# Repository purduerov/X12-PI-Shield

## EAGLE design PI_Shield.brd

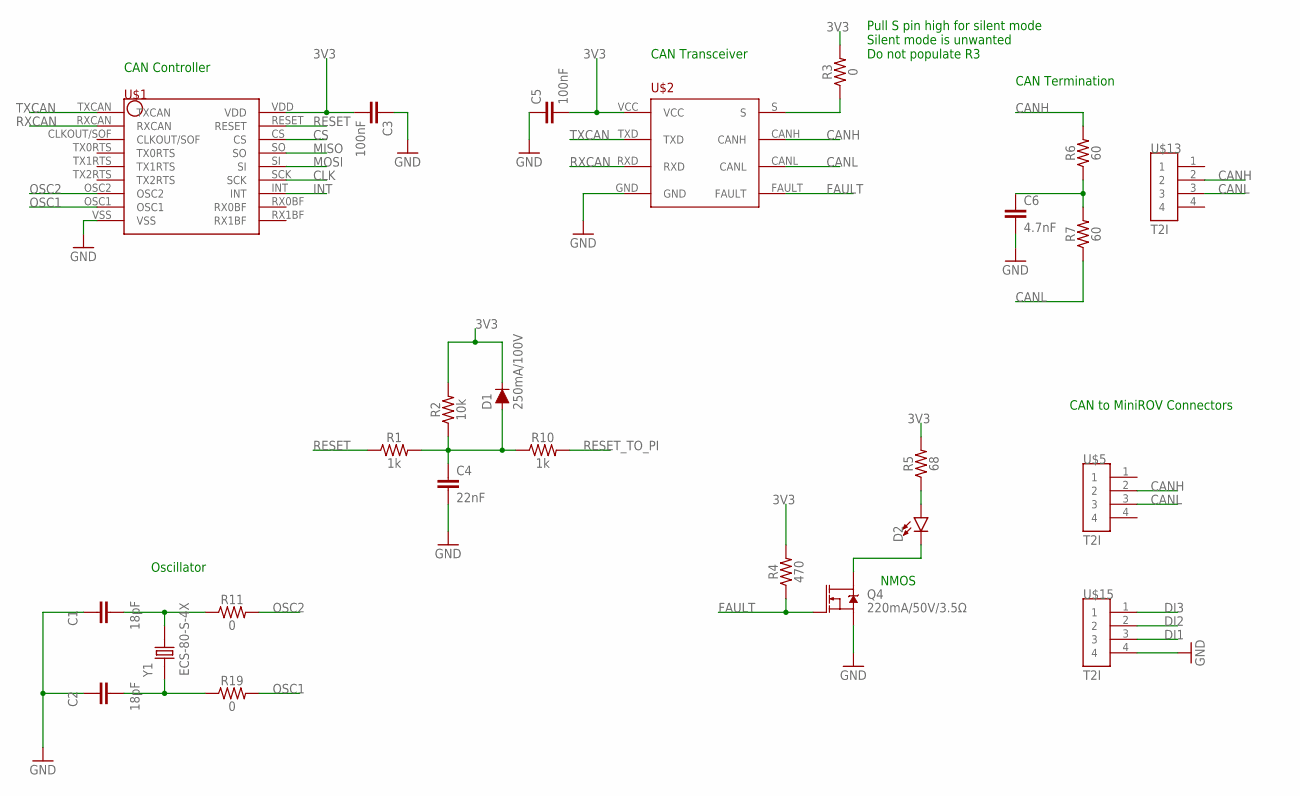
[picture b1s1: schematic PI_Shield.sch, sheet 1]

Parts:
C1, C2: 18pF; CAP_0603
C3, C5: 100nF; 0603
C4: 22nF; 0603
C6: 4.7nF; 0603
D1: 250mA/100V; SOD-323
D2: LED0603; LED-0603
Q4: 220mA/50V/3.5Ω; SOT23-3
R1, R10: 1k; 0603
R2: 10k; 0603
R3, R11, R19: 0; 0603
R4: 470; 0603
R5: 68; 0603
R6, R7: 60; 0603
U$1: MCP2515
U$2: TCAN337D
U$5, U$13, U$15: T2I
Y1: ECS-80-S-4X; XTAL_ECS-80-S-4X

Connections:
3V3: C3.2, C5.2, D1.C, R2.2, R3.2, R4.2, R5.2, U$1.VDD, U$2.VCC; also elsewhere on the board
CANH: R6.2, U$2.CANH, U$5.2, U$13.2; also elsewhere on the board
CANL: R7.1, U$2.CANL, U$5.3, U$13.3; also elsewhere on the board
CLK: U$1.SCK; also elsewhere on the board
CS: U$1.CS; also elsewhere on the board
DI1: U$15.3; also elsewhere on the board
DI2: U$15.2; also elsewhere on the board
DI3: U$15.1; also elsewhere on the board
FAULT: Q4.1 (G), R4.1, U$2.FAULT
GND: C1.1, C2.1, C3.1, C4.2, C5.1, C6.2, Q4.2 (S), U$1.VSS, U$2.GND, U$15.4; also elsewhere on the board
INT: U$1.INT; also elsewhere on the board
MISO: U$1.SO; also elsewhere on the board
MOSI: U$1.SI; also elsewhere on the board
unnamed: R3.1, U$2.S
unnamed: C1.2, R11.1, Y1.2
unnamed: C2.2, R19.1, Y1.1
unnamed: C6.1, R6.1, R7.2
unnamed: D2.C, Q4.3 (D)
unnamed: D2.A, R5.1
unnamed: C4.1, D1.A, R1.2, R2.1, R10.1
OSC1: R19.2, U$1.OSC1
OSC2: R11.2, U$1.OSC2
RESET: R1.1, U$1.RESET
RESET_TO_PI: R10.2; also elsewhere on the board
RXCAN: U$1.RXCAN, U$2.RXD
TXCAN: U$1.TXCAN, U$2.TXD

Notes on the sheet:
Oscillator
CAN Controller
CAN Transceiver
CAN Termination
CAN to MiniROV Connectors
NMOS
Pull S pin high for silent mode Silent mode is unwanted Do not populate R3

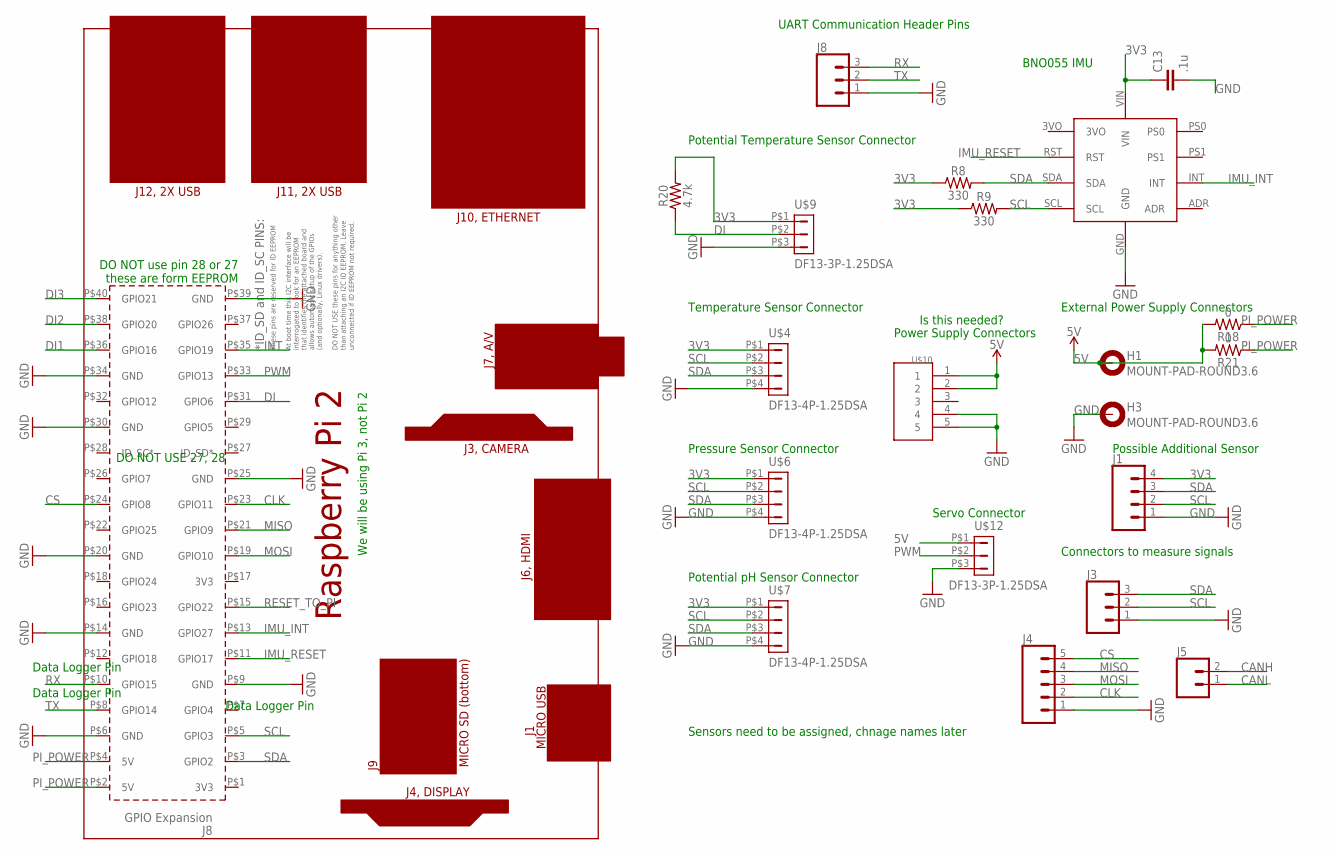
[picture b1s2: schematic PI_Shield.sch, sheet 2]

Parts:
C13: .1u; 0603
H1, H3: MOUNT-PAD-ROUND3.6; 3,6-PAD
J1: CONN_04; 1X04
J3, J8: CONN_03; 1X03
J4: CONN_05; 1X05
J5: CONN_02; 1X02
PCB1: RPI2
R8, R9: 330; 0603
R18, R21: 0; 0603
R20: 4.7k; 0603
U$3: BNO055_9DOF_BREAKOUT; BNO055
U$4, U$6, U$7: DF13-4P-1.25DSA
U$9, U$12: DF13-3P-1.25DSA
U$10: T2I5P

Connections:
3V3: C13.1, J1.4, R8.1, R9.1, R20.2, U$3.VIN, U$4.P$1 (1), U$6.P$1 (1), U$7.P$1 (1), U$9.P$1 (1); also elsewhere on the board
5V: H1.B3,6, R18.2, R21.2, U$10.1, U$10.2, U$12.P$1 (1); also elsewhere on the board
CANH: J5.2; also elsewhere on the board
CANL: J5.1; also elsewhere on the board
CLK: J4.2, PCB1.P$23 (GPIO11); also elsewhere on the board
CS: J4.5, PCB1.P$24 (GPIO8); also elsewhere on the board
DI: PCB1.P$31 (GPIO6), R20.1, U$9.P$2 (2)
DI1: PCB1.P$36 (GPIO16); also elsewhere on the board
DI2: PCB1.P$38 (GPIO20); also elsewhere on the board
DI3: PCB1.P$40 (GPIO21); also elsewhere on the board
GND: C13.2, H3.B3,6, J1.1, J3.1, J4.1, J8.1, PCB1.P$6 (GND), PCB1.P$9 (GND), PCB1.P$14 (GND), PCB1.P$20 (GND), PCB1.P$25 (GND), PCB1.P$30 (GND), PCB1.P$34 (GND), PCB1.P$39 (GND), U$3.GND, U$4.P$4 (4), U$6.P$4 (4), U$7.P$4 (4), U$9.P$3 (3), U$10.4, U$10.5, U$12.P$3 (3); also elsewhere on the board
IMU_INT: PCB1.P$13 (GPIO27), U$3.INT
IMU_RESET: PCB1.P$11 (GPIO17), U$3.RST
INT: PCB1.P$35 (GPIO19); also elsewhere on the board
MISO: J4.4, PCB1.P$21 (GPIO9); also elsewhere on the board
MOSI: J4.3, PCB1.P$19 (GPIO10); also elsewhere on the board
PI_POWER: PCB1.P$2 (5V), PCB1.P$4 (5V), R18.1, R21.1
PWM: PCB1.P$33 (GPIO13), U$12.P$2 (2)
RESET_TO_PI: PCB1.P$15 (GPIO22); also elsewhere on the board
RX: J8.3, PCB1.P$10 (GPIO15)
SCL: J1.2, J3.2, PCB1.P$5 (GPIO3), R9.2, U$3.SCL, U$4.P$2 (2), U$6.P$2 (2), U$7.P$2 (2); also elsewhere on the board
SDA: J1.3, J3.3, PCB1.P$3 (GPIO2), R8.2, U$3.SDA, U$4.P$3 (3), U$6.P$3 (3), U$7.P$3 (3); also elsewhere on the board
TX: J8.2, PCB1.P$8 (GPIO14)

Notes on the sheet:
Connectors to measure signals
Temperature Sensor Connector
Pressure Sensor Connector
Potential pH Sensor Connector
BNO055 IMU
External Power Supply Connectors
Potential Temperature Sensor Connector
Power Supply Connectors
Possible Additional Sensor
UART Communication Header Pins
Servo Connector
Is this needed?
Data Logger Pin
We will be using Pi 3, not Pi 2
Sensors need to be assigned, chnage names later
DO NOT use pin 28 or 27 these are form EEPROM
DO NOT USE 27, 28

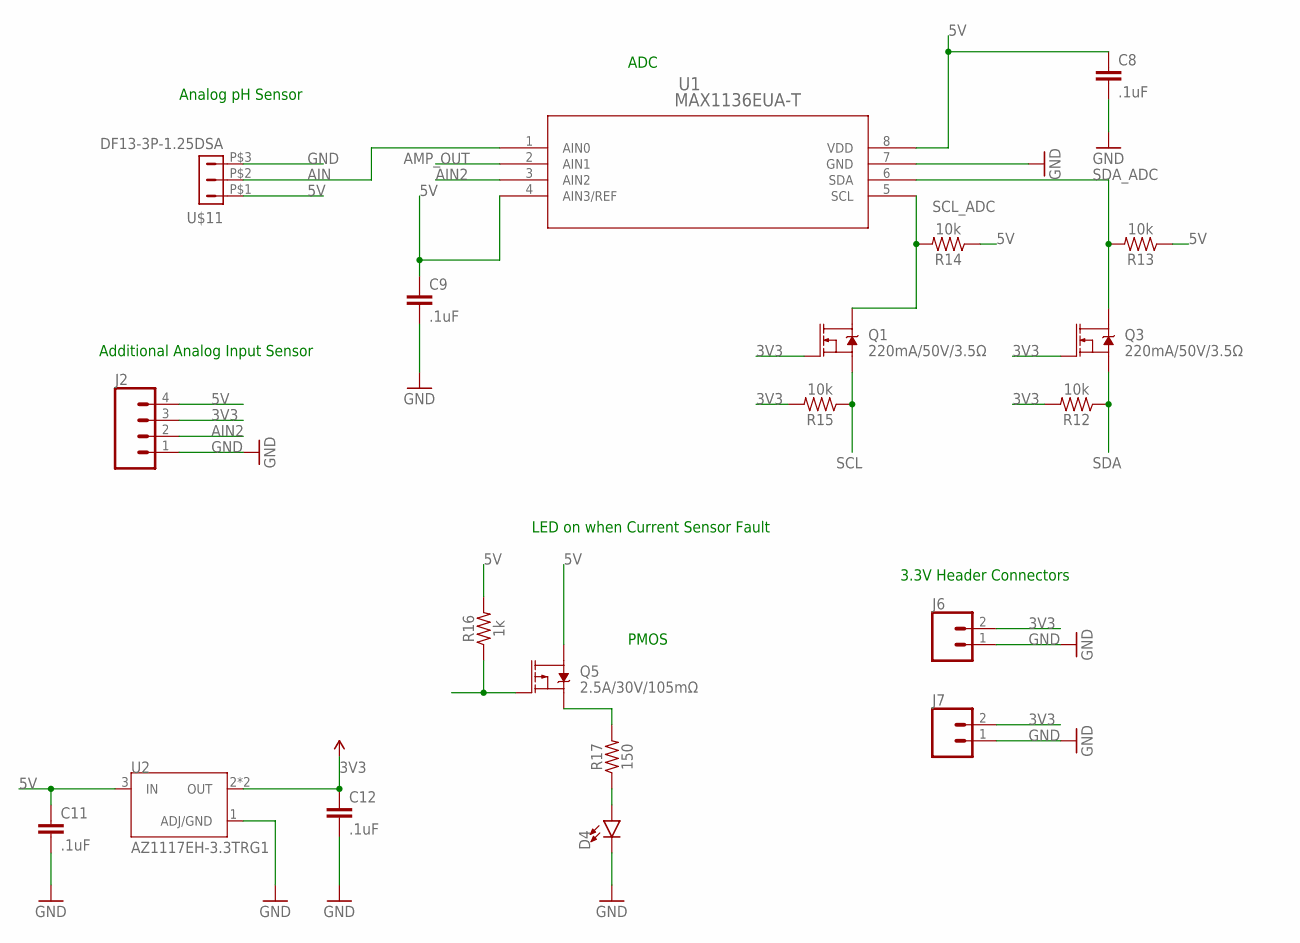
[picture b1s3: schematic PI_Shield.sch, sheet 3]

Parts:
C8, C9, C11, C12: .1uF; 0603
D4: LED0603; LED-0603
J2: CONN_04; 1X04
J6, J7: CONN_02; 1X02
Q1, Q3: 220mA/50V/3.5Ω; SOT23-3
Q5: 2.5A/30V/105mΩ; SOT23-3
R12, R13, R14, R15: 10k; 0603
R16: 1k; 0603
R17: 150; 0603
U1: MAX1136EUA-T; 21-0036K
U2: AZ1117EH-3.3TRG1; SOT230P700X180-4N
U$11: DF13-3P-1.25DSA

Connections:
3V3: C12.1, J2.3, J6.2, J7.2, Q1.1 (G), Q3.1 (G), R12.2, R15.2, U2.2 (OUT), U2.4 (OUT); also elsewhere on the board
5V: C8.1, C9.1, C11.1, J2.4, Q5.3 (D), R13.1, R14.1, R16.2, U1.4 (AIN3/REF), U1.8 (VDD), U2.3 (IN), U$11.P$1 (1); also elsewhere on the board
AIN: U1.1 (AIN0), U$11.P$2 (2)
AIN2: J2.2, U1.3 (AIN2)
AMP_FAULT: Q5.1 (G), R16.1
AMP_OUT: U1.2 (AIN1)
GND: C8.2, C9.2, C11.2, C12.2, D4.C, J2.1, J6.1, J7.1, U1.7 (GND), U2.1 (ADJ/GND), U$11.P$3 (3); also elsewhere on the board
unnamed: Q5.2 (S), R17.2
unnamed: D4.A, R17.1
SCL: Q1.2 (S), R15.1; also elsewhere on the board
SCL_ADC: Q1.3 (D), R14.2, U1.5 (SCL)
SDA: Q3.2 (S), R12.1; also elsewhere on the board
SDA_ADC: Q3.3 (D), R13.2, U1.6 (SDA)

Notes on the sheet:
Analog pH Sensor
ADC
Additional Analog Input Sensor
3.3V Header Connectors
PMOS
LED on when Current Sensor Fault

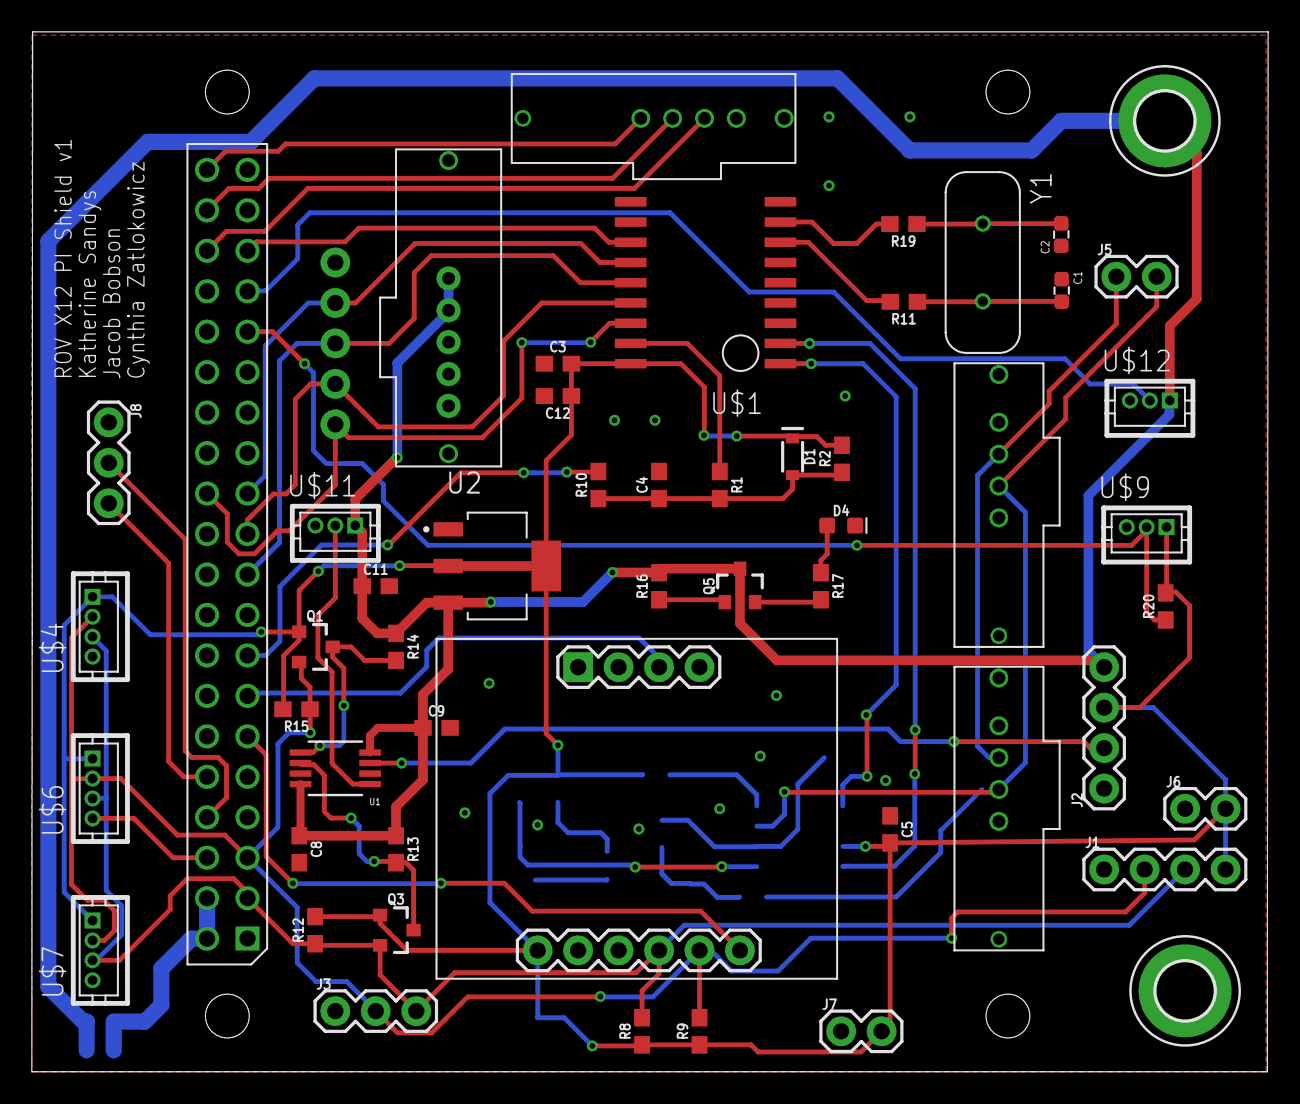
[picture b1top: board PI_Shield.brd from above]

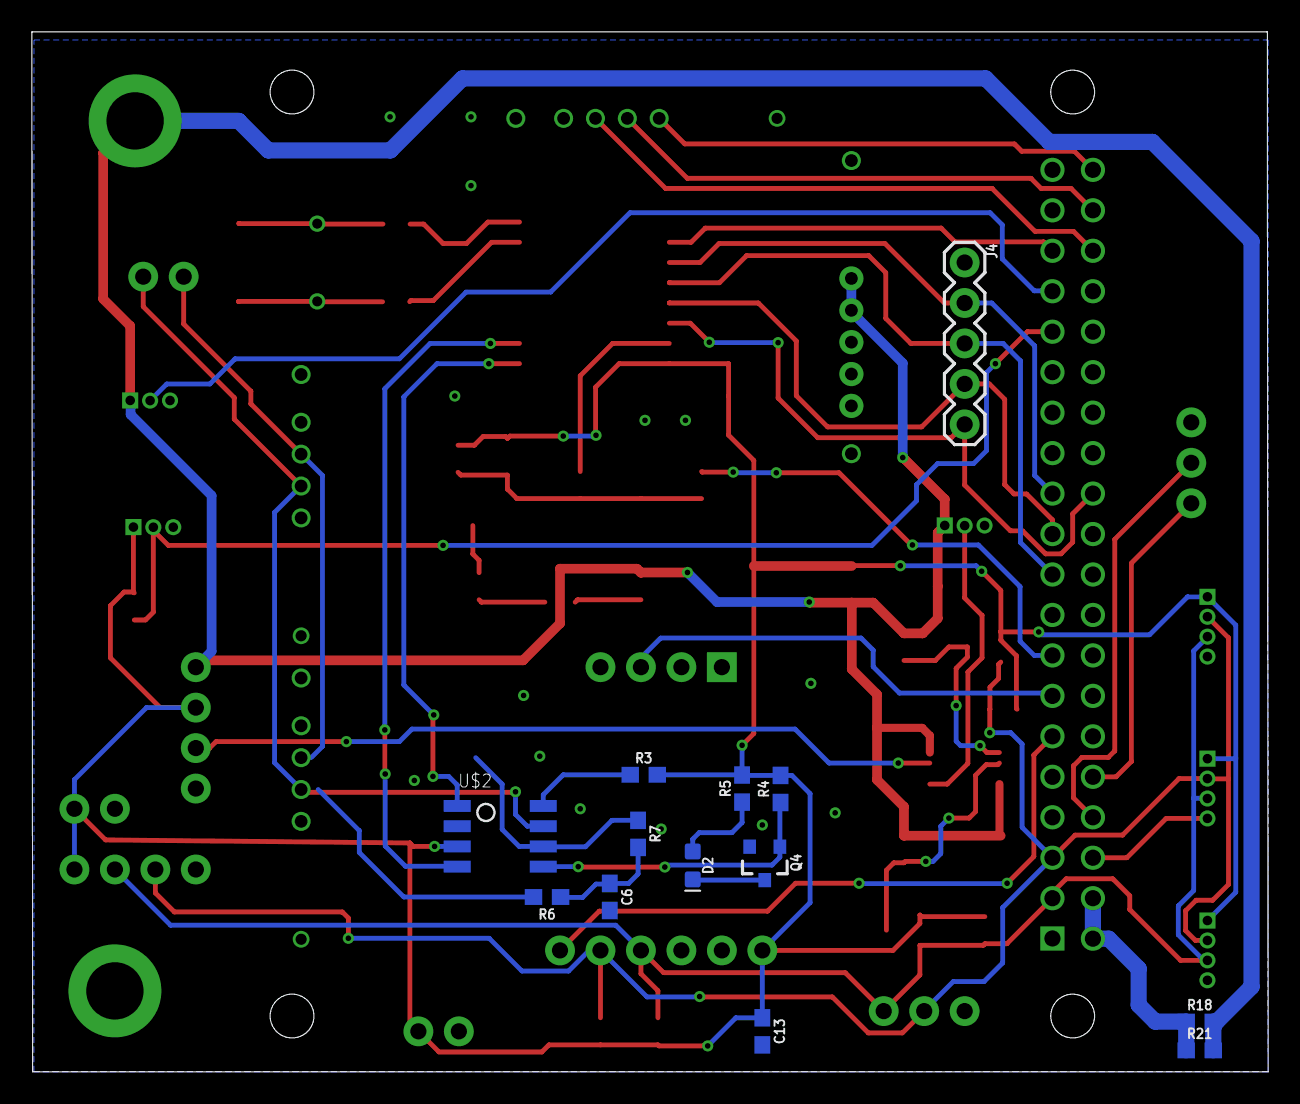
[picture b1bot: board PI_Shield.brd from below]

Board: 2 copper layers, 77.6 x 65.3 mm, 66 parts (13 on the bottom side), 43 nets.

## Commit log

2019-10-23 Fixes for the GND
2019-10-23 wires setup
2019-10-25 Finished the wiring
2019-10-27 fixed some errors
2019-10-30 Length of wires updated
2019-11-02 Outline change
2019-12-30 Labels and DRC
2019-12-31 Fixed capacitor for CAN transciever
2019-12-31 put seahorse image on
2020-01-02 Final Changes
2020-01-07 GPIO Power
2020-02-16 added DXF for Keith
2020-02-16 added gitignore and removed old files
2020-03-06 added note not to populate jumper
2020-09-01 Added comment
    Added comment to not use two pins so that way board will not afect pi 4 boot-up
2020-09-12 cad for 4 pin samtec t2i
2020-09-13 cad for 5 pin samtec t2i. had to reroute spi signals for larger t2i soldering area

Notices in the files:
parts and their libraries:
SparkFun-Capacitors: Licensing: Creative Commons ShareAlike 4.0 International - https://creativecommons.org/licenses/by-sa/4.0
